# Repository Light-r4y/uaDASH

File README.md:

# uaDASH

## TL,DR

See https://github.com/Light-r4y/uaDASH/releases for official release which include pre-compiled binaries and flashing utility!

## rusEFI open source ultra affordable CAN-bus dashboard

The device can display engine operating parameters and bench test coils and injectors.

The project can work on 
* GUITION JC8048W550C
* Waveshare ESP32-S3-Touch-LCD-5 800x480
* Waveshare ESP32-S3-Touch-LCD-7 800x480

For change brightness use swipe up/down on main screen (ESP32-S3-Touch-LCD-7 if solder 1 wire, ESP32-S3-Touch-LCD-5 not tested).

Change main/bench/settings screen use swipe left/right.

For save settings after reboot/power cycle need press "Save" button.

Bench test screen:

Settings screen:

-------------------------------------------------------------------

## Build with Arduino CLI

```
arduino-cli core update-index
arduino-cli lib install lvgl@8.4.0
arduino-cli lib install LovyanGFX@1.2.0
arduino-cli lib install ESP32_IO_Expander@1.1.0
arduino-cli core install esp32:esp32@3.2.1
arduino-cli -j16 compile -b esp32:esp32:esp32s3:FlashSize=16M,PartitionScheme=app3M_fat9M_16MB,PSRAM=opi,EventsCore=0 --build-property "compiler.cpp.extra_flags=-D<set-you-dislay> -O2" firmware.ino --output-dir ./artifacts -v
arduino-cli upload -b esp32:esp32:esp32s3:FlashSize=16M,PartitionScheme=app3M_fat9M_16MB,PSRAM=opi,EventsCore=0 --build-path ./artifacts -p <you-display-COMport> -v
```

-------------------------------------------------------------------

## Flash for use ESP Web flasher
https://espressif.github.io/esptool-js/

1. Press "Connect"
2. Select you connected display COM port (maybe can use boot button on board, for into bootloader mode)
3. Press "Erase flash" (optional)
4. Set flash address 0x0 -> add file "firmware.ino.bootloader.bin"
5. Set flash address 0x8000 -> add file "firmware.ino.partitions.bin"
6. Set flash address 0x10000 -> add file "firmware.ino.bin"
7. Press "Program"
8. Wait and watch carefully as the inscriptions appear on the black screen.
9. If you watch "Hard resetting via RTS pin...", press RST button on board and be happy! Else sad and try repeat or check you binary files.

-------------------------------------------------------------------

## Build settings if use Arduino IDE

(maybe for best performance compile with -O2/O3 flag)

Required library:
- ESP32 Core v3.2.1 (new version is not built now)

- LVGL v8 (graphic lib)

- LovyanGFX (display driver)

- ESP32_IO_Expander@1.1.0 (if use Waveshare board)

[README-GUITION.md](README-GUITION.md)

[README-ESP32-S3-Touch-LCD-5.md](README-ESP32-S3-Touch-LCD-5.md)

[README-ESP32-S3-Touch-LCD-7.md](README-ESP32-S3-Touch-LCD-7.md)

## FAQ

### Q: which of three supported screens is best?

A: ESP32-S3-Touch-LCD-5 from Waveshare has both on-board CAN transceiver and on-board 12v power supply, that one you just need to connect to vehicle!

### Q: why only 800x480?

A: With limited software developers availability, we focus on only one resolution. Sorry, no 1024x600.

### Q: To edit the dash, is it just a world of manually editing the ui_mainscreen.c?

A: made with https://squareline.io/

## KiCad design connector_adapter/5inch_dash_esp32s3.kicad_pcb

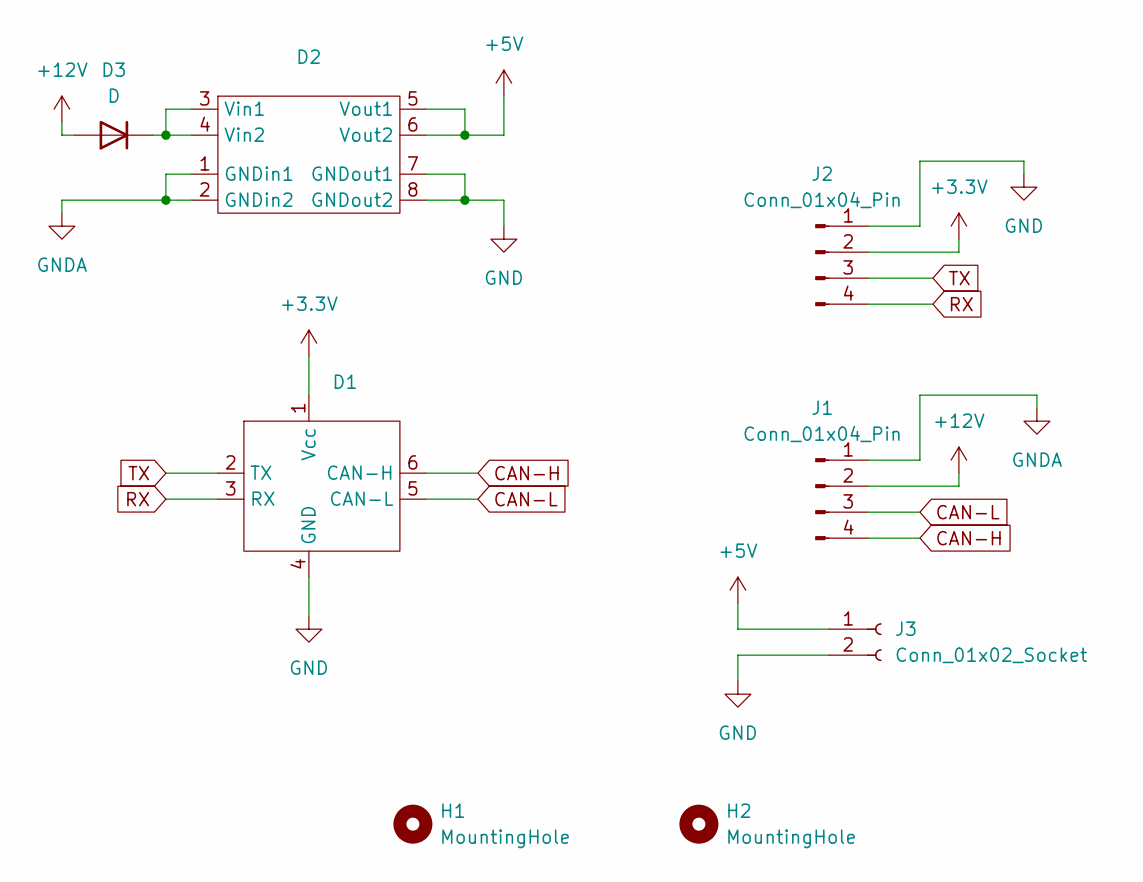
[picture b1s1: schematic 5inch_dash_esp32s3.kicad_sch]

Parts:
D1: TJA1050Module
D2: mp1584
D3: D; D_SMB_Handsoldering
H1, H2: MountingHole; MountingHole_2.2mm_M2_DIN965
J1: Conn_01x04_Pin; JST_EH_B4B-EH-A_1x04_P2.50mm_Vertical
J2: Conn_01x04_Pin; wire-4-2.54
J3: Conn_01x02_Socket; wire-2-2.54

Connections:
+3.3V: D1.1 (Vcc), J2.2
+5V: D2.5 (Vout1), D2.6 (Vout2), J3.1
+12V: D3.2 (A), J1.2
CAN-H: D1.6 (CAN-H), J1.4
CAN-L: D1.5 (CAN-L), J1.3
GND: D1.4 (GND), D2.7 (GNDout1), D2.8 (GNDout2), J2.1, J3.2
GNDA: D2.1 (GNDin1), D2.2 (GNDin2), J1.1
unnamed: D2.3 (Vin1), D2.4 (Vin2), D3.1 (K)
RX: D1.3 (RX), J2.4
TX: D1.2 (TX), J2.3

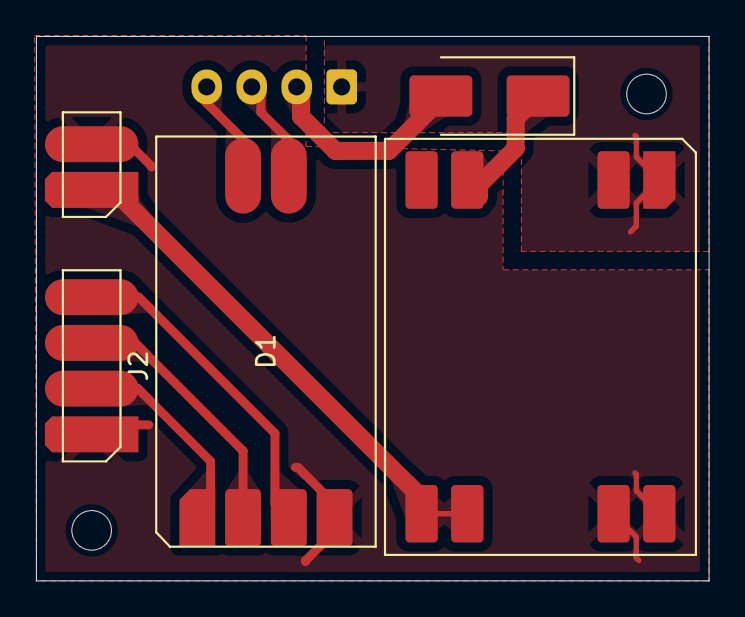
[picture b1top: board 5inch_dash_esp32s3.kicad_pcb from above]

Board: 2 copper layers, 37.4 x 30.2 mm, 8 parts (1 on the bottom side), 10 nets.

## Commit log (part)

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2025-03-05 initial
2025-03-05 add case files
2025-03-05 add adruino settings img
2025-04-23 fix white screen
2025-06-03 fix brightness settings
2025-06-03 rename
2025-06-03 esp32s3
    esp32:esp32
    Compile Sketch
    fqbn
2025-06-03 windows
2025-06-03 arduino-cli lib install lvgl
    arduino-cli lib install LovyanGFX@1.2.0
2025-06-03 artifact
2025-06-04 add bechtest screen
2025-06-04 fix ino
2025-06-09 small refactor
2025-06-10 add wiveshare displays (without real test)
2025-06-10 add square line project
2025-06-12 nicer file name
2025-06-12 progress
2025-06-12 magic commands
2025-06-14 major refactor
2025-06-14 new library
2025-06-14 change to build for 5"
2025-06-14 add bech CAN send status
2025-06-14 add bench IGN + INJ (worked on 7")
2025-06-15 fix 5" canbus
2025-06-16 add check for display selection, update media
2025-06-16 readme update
2025-06-16 update sq prj
2025-06-24 add settings screen
2025-06-26 add support WAVESHARE ESP32-S3-Touch-LCD-5
2025-06-26 add brightness adjustment for 7"
2025-06-26 WYSIWYG
2025-06-27 hello matrix
2025-06-27 unique artifact names
2025-06-27 when executed by github actions we want display variable to defined externally
2025-06-27 passing to .ino?
2025-06-27 fix CI matrix
2025-06-27 try fix
2025-06-27 try fix 2
2025-06-27 try fix 3
2025-06-27 try fix 3.5
2025-06-27 try fix 4
2025-06-27 try fix 4.5
2025-06-27 try fix CI 4.7
2025-06-27 try fix CI 4.8
2025-06-27 try fix CI 4.9
2025-06-27 try fix CI 5
2025-06-27 try fix CI 5.1
2025-06-27 try fix CI 5.2
2025-06-27 try fix -O2 flag
2025-06-27 Adding help into artifact folder
2025-06-27 reducing Windows distraction
2025-06-27 esp32.esp32.esp32s3
2025-06-27 docs progress
2025-06-27 README-ESP32-S3-Touch-LCD-5.md
2025-06-28 update Waveshare-5 readme
2025-06-28 one click flash firmware
2025-07-01 add Start/stop event
2025-07-04 add LS engine combo box control
2025-07-04 usability: esptool.exe into release
2025-07-04 .gitattributes
2025-07-04 fixing paths within release artifact
2025-07-05 release/release.txt
2025-07-05 add heartbeats, probaly fix Waveshare displays
2025-07-05 CI matrix fix
2025-07-06 hopefully smarter choice of EOL
2025-07-06 byte order is hard
2025-07-07 fix reboot
2025-07-09 we have .md
2025-07-09 1024x600
2025-07-15 add support Sunton_S3_LCD7
2025-08-02 probably fix prj clear flash
2025-08-02 daily build
2025-08-02 dash to display some sort of version #36 DASH_TAG skeleton
2025-08-03 add FW info in WarnSettings srceen
2025-08-03 IDE setting, hopefully not too much trouble
2025-08-03 current_date.sh
2025-08-03 fix turbo map
2025-08-12 add can_common, Sq projects update
2025-08-12 fix uint8_t
2025-08-12 fix uint32_t
2025-09-29 TL,DR
2025-10-01 spelling out "open source"
2025-10-02 fix CANbus reinit after ALERT_BUS_ERROR
2025-10-03 fix visual artifacts on WSH_5inch
2025-10-27 *** MAKE SURE TO UNPLUG 12v power while updating firmware via USB ***
2025-11-22 init tcu_nano
2025-11-22 update _screen
2025-11-22 current gear view
2025-11-22 add gear change events
2025-11-22 CAN bus fail restart
2026-04-28 docs
